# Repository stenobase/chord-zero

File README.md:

# CHORD ZERO Stenographic Keyboard

CHORD ZERO is a stenographic keyboard that can be used with
[Plover](https://www.openstenoproject.org/plover/) or any other application
that supports the [TX
Bolt](https://docs.qmk.fm/#/feature_stenography?id=tx-bolt) or
[GeminiPR](https://docs.qmk.fm/#/feature_stenography?id=geminipr) protocol.

## Build your own

### Create gerber files and order a PCB

The easiest way to create gerber files is with
[KiKit](https://github.com/yaqwsx/KiKit); and the easiest way to install
`KiKit` is with [pipx](https://pypa.github.io/pipx/):

```
$ pipx install kikit --system-site-packages
$ kikit fab <your_fab_of_choice> zero.kicad_pcb gerbers
```
This creates `gerbers/gerbers.zip`.  Use this file to order PCBs the same way
as you would usually do.

### Assembly

You will need the following parts:

1. 30x MX compatible switches
1. 30x key caps
1. 30x `1N4148W` (or similar)
1. 1x Raspberry Pi Pico
1. 1x `SMBJ5.0A` (or similar)
1. 2x `SK6812MINI` (optional)

You want linear switches with low actuation force. Gateron clears are a good
option.

You want key caps that minimize the gap between top and bottom row. Cherry
R2/R3 or OEM R3 are good options.

### Firmware

[Firmware and instructions are available here.](https://github.com/sol/qmk_firmware/tree/chord/keyboards/chord/zero#chord-zero-stenographic-keyboard)

## LICENSE

The CHORD ZERO Stenographic Keyboard is open source hardware.  You are
encouraged to produce your own keyboard based on the documentation and design
files of this project.  You are also encouraged to study and modify the design
and create derivatives.

- All documentation and design files of this project are released under the
  [CERN-OHL-S](LICENSE).
- Some of the used 3D models are licensed under the [MIT
  license](https://github.com/foostan/kbd/blob/master/LICENSE).
- The default firmware for this project is [QMK](https://qmk.fm/).  QMK is
  released under the terms of the [GNU General Public License, version
  2](https://qmk.fm/license/).
- All contributions to QMK that are specific to this project are released under
  the same terms as QMK itself.

<p align="center"></p>

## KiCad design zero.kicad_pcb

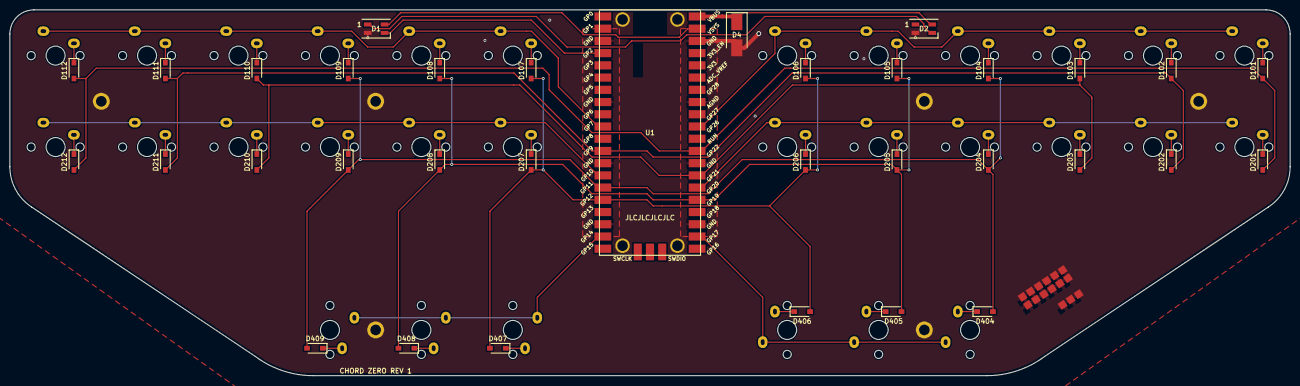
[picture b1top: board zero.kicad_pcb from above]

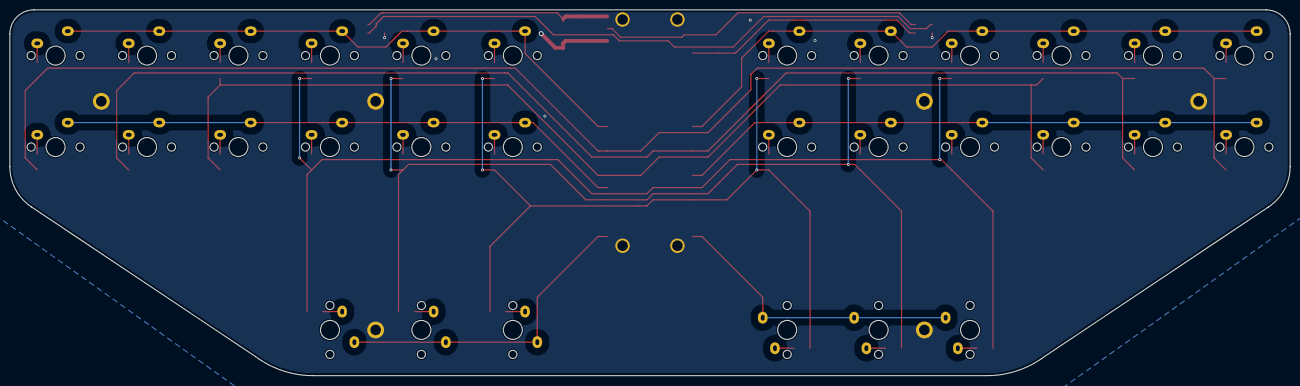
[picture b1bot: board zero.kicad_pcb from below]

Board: 2 copper layers, 266.0 x 76.0 mm, 75 parts (30 on the bottom side), 47 nets.

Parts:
D1, D2: SK6812MINI; LED_SK6812MINI_PLCC4_3.5x3.5mm_P1.75mm
D4: P6SMB6.8A; D_SMB_Handsoldering
D101, D102, D103, D104, D105, D106, D107, D108, D109, D110, D111, D112, D201, D202, D203, D204, D205, D206, D207, D208, D209, D210, D211, D212, D404, D405, D406, D407, D408, D409: 1N4148W; D_SOD-123
H1, H2, H3, H4, H5, H6: MountingHole; M2 Hole
H7, H8, H9, H10: MountingHole Pico; M2 Hole Pico
LOGO_1: CHORD LOGO; chord_logo_3d
SW101, SW102, SW103, SW104, SW105, SW106, SW107, SW108, SW109, SW110, SW111, SW112, SW201, SW202, SW203, SW204, SW205, SW206, SW207, SW208, SW209, SW210, SW211, SW212, SW404, SW405, SW406, SW407, SW408, SW409: SW_Push; CherryMX_1u_snug_fit
U1: Pico; RPi_Pico_SMD

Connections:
+5V: D1.4 (VDD), U1.39 (VSYS)
/COL1: D101.2 (A), D112.2 (A), D201.2 (A), D212.2 (A), U1.29 (GPIO22)
/COL2: D102.2 (A), D111.2 (A), D202.2 (A), D211.2 (A), U1.12 (GPIO9)
/COL3: D103.2 (A), D110.2 (A), D203.2 (A), D210.2 (A), U1.27 (GPIO21)
/COL4: D104.2 (A), D109.2 (A), D204.2 (A), D209.2 (A), D404.2 (A), D409.2 (A), U1.15 (GPIO11)
/COL5: D105.2 (A), D108.2 (A), D205.2 (A), D208.2 (A), D405.2 (A), D408.2 (A), U1.25 (GPIO19)
/COL6: D106.2 (A), D107.2 (A), D206.2 (A), D207.2 (A), D406.2 (A), D407.2 (A), U1.16 (GPIO12)
/DIN_DOUT: D1.1 (DOUT), D2.3 (DIN)
/RGB: D1.3 (DIN), U1.4 (GPIO2)
/ROW1: SW101.2, SW102.2, SW103.2, SW104.2, SW105.2, SW106.2, U1.31 (GPIO26_ADC0)
/ROW2: SW201.2, SW202.2, SW203.2, SW204.2, SW205.2, SW206.2, U1.26 (GPIO20)
/ROW4: SW404.2, SW405.2, SW406.2, U1.22 (GPIO17)
/ROW5: SW107.2, SW108.2, SW109.2, SW110.2, SW111.2, SW112.2, U1.10 (GPIO7)
/ROW6: SW207.2, SW208.2, SW209.2, SW210.2, SW211.2, SW212.2, U1.14 (GPIO10)
/ROW8: SW407.2, SW408.2, SW409.2, U1.19 (GPIO14)
GND: D1.2 (VSS), D2.2 (VSS), D4.2 (A), H1.1, H2.1, H3.1, H4.1, H5.1, H6.1, H7.1, H8.1, H9.1, H10.1, LOGO_1.1, U1.3 (GND), U1.8 (GND), U1.13 (GND), U1.18 (GND), U1.23 (GND), U1.28 (GND), U1.33 (AGND), U1.38 (GND)
unnamed: D101.1 (K), SW101.1
unnamed: D102.1 (K), SW102.1
unnamed: D103.1 (K), SW103.1
unnamed: D104.1 (K), SW104.1
unnamed: D105.1 (K), SW105.1
unnamed: D106.1 (K), SW106.1
unnamed: D107.1 (K), SW107.1
unnamed: D108.1 (K), SW108.1
unnamed: D109.1 (K), SW109.1
unnamed: D110.1 (K), SW110.1
unnamed: D111.1 (K), SW111.1
unnamed: D112.1 (K), SW112.1
unnamed: D201.1 (K), SW201.1
unnamed: D202.1 (K), SW202.1
unnamed: D203.1 (K), SW203.1
unnamed: D204.1 (K), SW204.1
unnamed: D205.1 (K), SW205.1
unnamed: D206.1 (K), SW206.1
unnamed: D207.1 (K), SW207.1
unnamed: D208.1 (K), SW208.1
unnamed: D209.1 (K), SW209.1
unnamed: D210.1 (K), SW210.1
unnamed: D211.1 (K), SW211.1
unnamed: D212.1 (K), SW212.1
unnamed: D404.1 (K), SW404.1
unnamed: D405.1 (K), SW405.1
unnamed: D406.1 (K), SW406.1
unnamed: D407.1 (K), SW407.1
unnamed: D408.1 (K), SW408.1
unnamed: D409.1 (K), SW409.1
VBUS: D2.4 (VDD), D4.1 (K), U1.40 (VBUS)

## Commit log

2022-06-20 REV 0
2022-08-17 Move placeholder for order number
2022-08-17 Remove WS2812B
2022-08-17 Extend ground pour to both sides
2022-08-17 Add edge clearance for ground pours
    - Change mounting holes for pico to PTHs
    - Connect RGB power to VSYS instead of VBUS (this gives us more
    clearance around the mounting holes and should work equally well)
2022-08-17 Adjust SOD-123 silk
2022-08-17 REV 1
2022-08-18 Add logo on backside
